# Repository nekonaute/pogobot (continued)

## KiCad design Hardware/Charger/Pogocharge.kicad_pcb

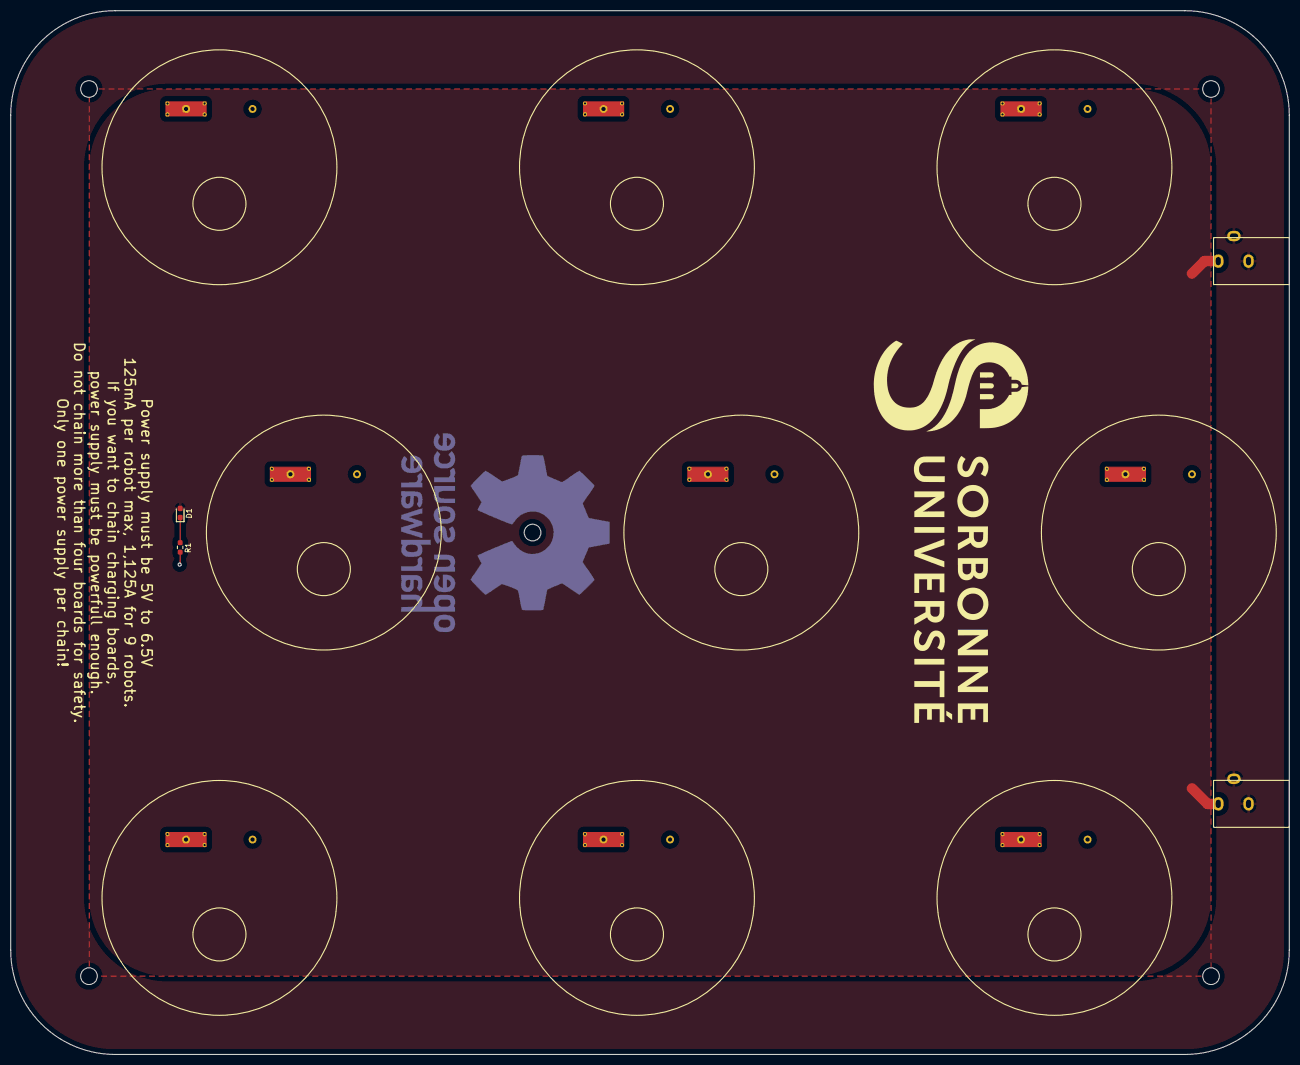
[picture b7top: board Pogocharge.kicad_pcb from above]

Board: 2 copper layers, 245.0 x 200.0 mm, 22 parts (0 on the bottom side), 3 nets.

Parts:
D1: LED; LED_0603_1608Metric_Pad1.05x0.95mm_HandSolder
J1, J4: Barrel_Jack_Switch; Barrel Jack_SparkFun_PRT-10811
J6, J8, J9, J10, J11, J19, J20, J21, J22: 90224-AS; 90224-AS-plus
J12, J13, J15, J16, J17, J23, J24, J25, J26: 90224-AS; 90224-AS-minus
R1: 10k; R_0603_1608Metric_Pad0.98x0.95mm_HandSolder

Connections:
+5V: D1.2 (A), J1.1, J4.1
GND: J1.2, J1.3, J4.2, J4.3, J12.1, J13.1, J15.1, J16.1, J17.1, J23.1, J24.1, J25.1, J26.1, R1.2
unnamed: D1.1 (K), R1.1

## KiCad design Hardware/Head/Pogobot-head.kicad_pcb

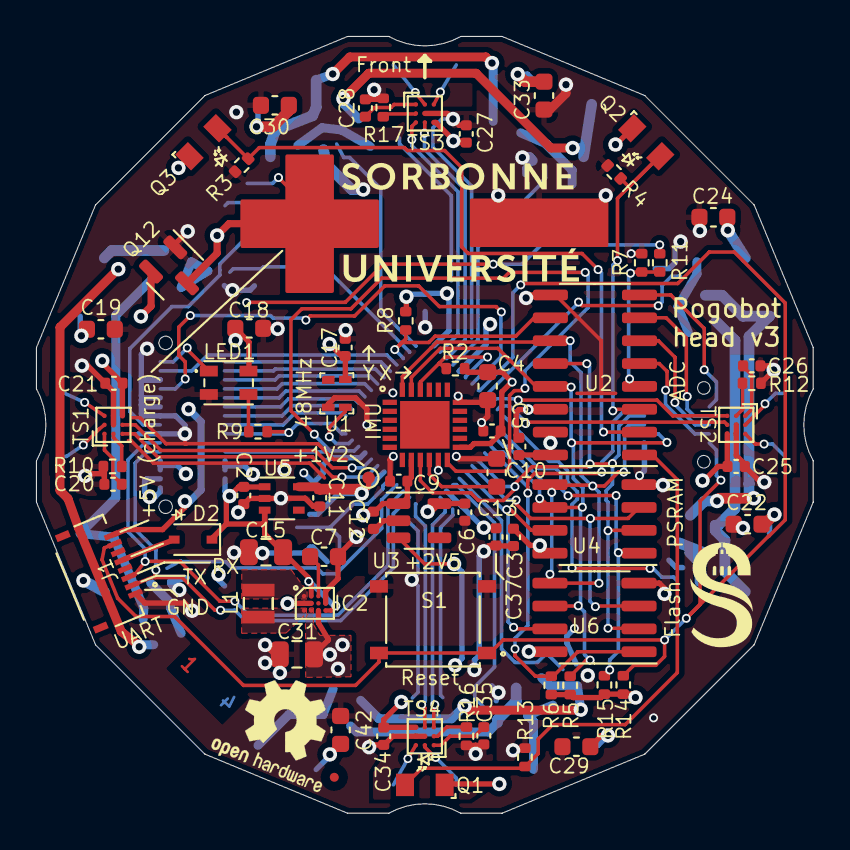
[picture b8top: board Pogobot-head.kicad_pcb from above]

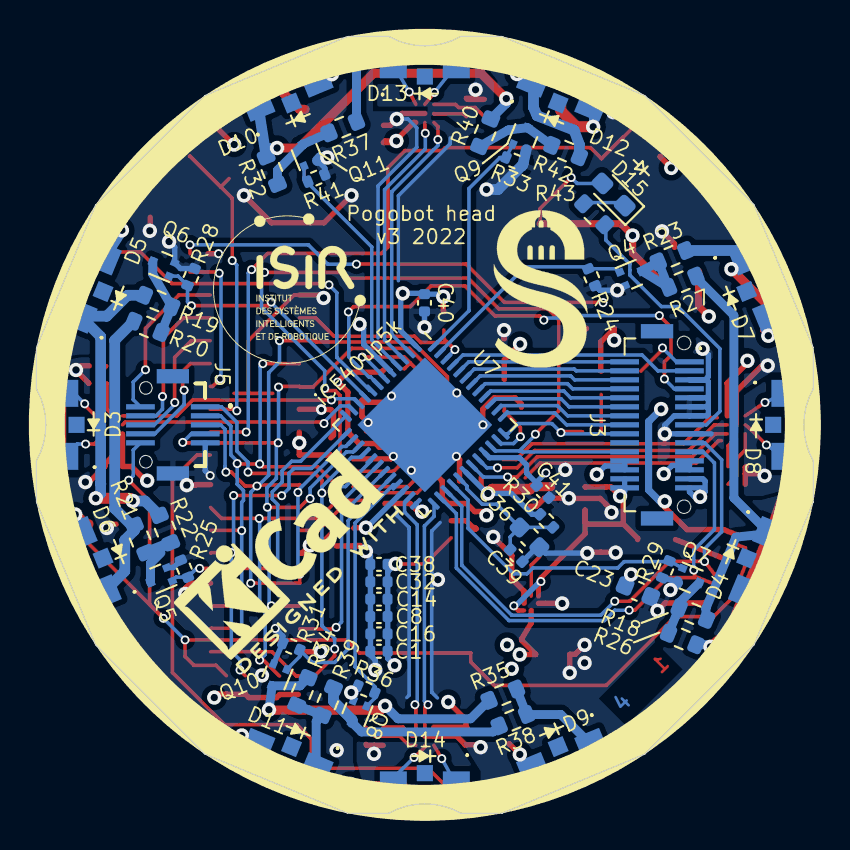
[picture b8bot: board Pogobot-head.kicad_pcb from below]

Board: 4 copper layers, 43.2 x 43.2 mm, 136 parts (64 on the bottom side), 98 nets.

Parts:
C1, C2, C5, C6, C11, C12, C14, C20, C26, C28, C35: 1uF; C_0402_1005Metric
C3, C16, C17, C37, C38, C39, C40, C41: 100nF; C_0402_1005Metric
C4: 2.2uF, X5R; C_0603_1608Metric
C7: 1uF, 10V; C_0603_1608Metric
C8, C32: 10nF; C_0402_1005Metric
C9: 10nF, X7R; C_0402_1005Metric
C10, C21, C25, C27, C34: 100nF, X7R; C_0402_1005Metric
C13: 470nF, X7R; C_0603_1608Metric
C15: 10uF, 10V; C_0805_2012Metric
C18, C36: 10uF; C_0603_1608Metric
C19, C22, C23, C24, C29, C30, C33, C42: 10uF, 6V; C_0603_1608Metric
C31: 22uF, 6V; C_0805_2012Metric
D2: 1N4448WS; D_SOD-323
D3, D8, D13, D14: VEMD10940F; VEMD10940FX01
D4, D5, D6, D7, D9, D10, D11, D12: VSMB10940
D15: LED; LED_0603_1608Metric_Pad1.05x0.95mm_HandSolder
IC1: ICM-20689; QFN50P400X400X95-25N-D
IC2: MAX77827DEWC+T; BGA12C40P4X3_201X161X69
J1: 2328702-8; 23287028
J3: 10132798-032100LF; 10132798032100LF
J5: 10132798-012100LF; 10132798012100LF
L1: MEKK2016H1R0M 1.0uH 41mOhms 4.5A; MEKK2016H
LED1: IN-PI22TAT5R5G5B; INPI22TAT5R5G5B
LOGO01: OSHW-Logo2_7.3x6mm_SilkScreen
LOGO02: KiCad-Logo2_5mm_SilkScreen
LOGO03: LOGO; LOGO_SU_without_text
LOGO04: LOGO; logo_isir_moyen
Q1, Q2, Q3: SFH 3710-Z; SFH3710
Q4, Q5, Q6, Q7, Q8, Q9, Q10, Q11: NTK3134NT5G; SOT-723
Q12: Q_PMOS_GSD; SOT-23
R2, R5, R6, R7, R8, R11, R14, R15, R24, R25, R28, R29, R31, R33, R36, R41: 10K; R_0402_1005Metric
R3, R4, R13: 1M; R_0402_1005Metric
R9: 330; R_0402_1005Metric
R10, R12, R16, R17: 15K; R_0402_1005Metric
R18, R19, R20, R26, R32, R37, R38, R39: 3; R_0603_1608Metric
R21, R22, R23, R27, R34, R35, R40, R42: 6; R_0603_1608Metric
R30: 100; R_0402_1005Metric
R43: 1K; R_0603_1608Metric
S1: PTS526_SM15_SMTR2_LFS; PTS526SK15SMTR2LFS
TP1: Testpoint; TestPoint_Pad_D0.7mm
TP2: TestPoint; Plus
TP3: TestPoint; Minus
TS1, TS2, TS3, TS4: TS4231; BGA-9_1.6x1.6mm_Layout3x3_P0.5mm
U1: DSC6101MI2B-048.0000; 4-Lead 2.0 mm x 1.6 mm VFLGA
U2: MCP3008; SOIC-16_3.9x9.9mm_P1.27mm
U3: MIC5504-2.5YM5; SOT-23-5
U4: LY68L6400; SOIC-8_3.9x4.9mm_P1.27mm
U5: MIC5365-1.2YC5; SOT-353_SC-70-5
U6: W25Q16JVSNIM; SOIC-8_3.9x4.9mm_P1.27mm
U7: ICE40UP5K-SG48; QFN-48-1EP_7x7mm_P0.5mm_EP5.3x5.3mm

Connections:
+1V2: C1.1, C8.1, C11.1, C14.1, C16.1, C32.1, C38.1, R30.2, TP1.1, U3.3 (EN), U5.5 (VOUT), U7.5 (VCC), U7.30 (VCC)
+2V5: C6.1, U3.5 (VOUT), U7.24 (VPP_2V5)
+3V3: C3.1, C4.1, C5.1, C9.1, C10.1, C12.1, C17.1, C18.1, C19.1, C21.1, C22.1, C23.1, C24.1, C25.1, C27.1, C29.1, C30.1, C31.1, C33.1, C34.1, C37.1, C40.1, C41.1, C42.1, D4.2, D5.2, D6.2, D7.2, D9.2, D10.2, D11.2, D12.2, IC1.8 (VDDIO), IC1.13 (VDD), IC2.C2 (OUT), IC2.C3 (OUTS), J3.12, J3.13, J3.18, J3.19, LED1.4 (VDD), Q1.1 (C), Q2.1 (C), Q3.1 (C), R2.1, R5.1, R6.1, R8.1, R14.1, R15.1, TS1.C3 (DVDD), TS2.C3 (DVDD), TS3.C3 (DVDD), TS4.C3 (DVDD), U1.4 (VDD), U2.15 (Vref), U2.16 (Vdd), U3.1 (VIN), U4.8 (VCC), U6.8 (VCC), U7.1 (VCCIO_2), U7.22 (SPI_VCCIO1), U7.33 (VCCIO_0)
+5V: J3.14, J3.15, Q12.2 (S)
+BATT: C2.1, C15.1, D2.1 (K), IC2.A2 (IN), IC2.C4 (EN), J3.16, J3.17, R11.1, U5.1 (VIN), U5.3 (EN)
/Back: Q1.2 (E), R13.1, U2.1 (CH0)
/CH4: J5.7, U2.5 (CH4)
/CH5: J5.8, U2.6 (CH5)
/CH6: J5.9, U2.7 (CH6)
/CH7: J5.10, U2.8 (CH7)
/Charge: D15.2 (A), J1.8, Q12.3 (D), TP2.1
/LX1: IC2.A1 (LX1), L1.2
/LX2: IC2.C1 (LX2), L1.1
/Left: Q3.2 (E), R3.1, U2.2 (CH1)
/OSC_IN: U1.3 (OUT), U7.35 (IOT_46B_G0)
/Right: Q2.2 (E), R4.1, U2.3 (CH2)
/VBat_control: R7.1, R11.2, U2.4 (CH3)
/VCCPLL: C36.1, C39.1, R30.1, U7.29 (VCCPLL)
/sheetReceive_Back/AVDD: C35.1, TS4.A1 (AVDD)
/sheetReceive_Back/IIN+: D14.2 (A), TS4.A2 (IIN+)
/sheetReceive_Back/IIN-: D14.1 (K), TS4.A3 (IIN-)
/sheetReceive_Back/RBIAS: R16.2, TS4.B1 (RBIAS)
/sheetReceive_Front/AVDD: C28.1, TS3.A1 (AVDD)
/sheetReceive_Front/IIN+: D13.2 (A), TS3.A2 (IIN+)
/sheetReceive_Front/IIN-: D13.1 (K), TS3.A3 (IIN-)
/sheetReceive_Front/RBIAS: R17.2, TS3.B1 (RBIAS)
/sheetReceive_Left/AVDD: C20.1, TS1.A1 (AVDD)
/sheetReceive_Left/IIN+: D8.2 (A), TS1.A2 (IIN+)
/sheetReceive_Left/IIN-: D8.1 (K), TS1.A3 (IIN-)
/sheetReceive_Left/RBIAS: R10.2, TS1.B1 (RBIAS)
/sheetReceive_Right/AVDD: C26.1, TS2.A1 (AVDD)
/sheetReceive_Right/IIN+: D3.2 (A), TS2.A2 (IIN+)
/sheetReceive_Right/IIN-: D3.1 (K), TS2.A3 (IIN-)
/sheetReceive_Right/RBIAS: R12.2, TS2.B1 (RBIAS)
ADC_CSn: R8.2, U2.10 (~CS/SHDN), U7.46 (IOB_0A)
CDONE: J3.4, U7.7 (CDONE)
Emit1_B: Q10.1 (G), R31.1, U7.20 (IOB_25B_G3)
Emit1_F: Q9.1 (G), R33.1, U7.48 (IOB_4A)
Emit1_L: Q4.1 (G), R24.1, U7.47 (IOB_2A)
Emit1_R: Q5.1 (G), R25.1, U7.12 (IOB_22A)
Emit2_B: Q8.1 (G), R36.1, U7.21 (IOB_23B)
Emit2_F: Q11.1 (G), R41.1, U7.4 (IOB_8A)
Emit2_L: Q7.1 (G), R29.1, U7.28 (IOT_41A)
Emit2_R: Q6.1 (G), R28.1, U7.9 (IOB_16A)
FLASH_CS: J5.1, R6.2, U6.1 (~CS), U7.16 (IOB_35b_SPI_CSN)
GND: C1.2, C2.2, C3.2, C4.2, C5.2, C6.2, C7.2, C8.2, C9.2, C10.2, C11.2, C12.2, C13.2, C14.2, C15.2, C16.2, C17.2, C18.2, C19.2, C20.2, C21.2, C22.2, C23.2, C24.2, C25.2, C26.2, C27.2, C28.2, C29.2, C30.2, C31.2, C32.2, C33.2, C34.2, C35.2, C36.2, C37.2, C38.2, C39.2, C40.2, C41.2, C42.2, IC1.11 (FSYNC), IC1.18 (GND), IC2.A4 (AGND), IC2.B1 (PGND), IC2.B2 (FPWM), IC2.B4 (SEL), J1.1, J3.3, J3.5, J3.6, J3.7, J3.9, J5.5, J5.MP2, LED1.2 (VSS), Q4.2 (S), Q5.2 (S), Q6.2 (S), Q7.2 (S), Q8.2 (S), Q9.2 (S), Q10.2 (S), Q11.2 (S), Q12.1 (G), R3.2, R4.2, R7.2, R10.1, R12.1, R13.2, R16.1, R17.1, R24.2, R25.2, R28.2, R29.2, R31.2, R33.2, R36.2, R41.2, S1.3 (NO_1), S1.4 (NO_2), TP3.1, TS1.B2 (AVSS), TS1.B3 (AVSS2), TS2.B2 (AVSS), TS2.B3 (AVSS2), TS3.B2 (AVSS), TS3.B3 (AVSS2), TS4.B2 (AVSS), TS4.B3 (AVSS2), U1.2 (GND), U2.9 (DGND), U2.14 (AGND), U3.2 (GND), U4.4 (VSS), U5.2 (GND), U6.4 (GND), U7.49 (PAD/GND)
GPIO0: J3.30, U7.44 (IOB_3B_G6)
GPIO1: J3.29, U7.43 (IOT_49A)
GPIO2: J3.28, U7.42 (IOT_51A)
GPIO3: J3.27, U7.41 (RGB2)
GPIO4: J3.26, U7.40 (RGB1)
GPIO5: J3.25, U7.39 (RGB0)
GPIO6: J3.24, U7.38 (IOT_50B)
GPIO7: J3.23, U7.37 (IOT_45A_G1)
GPIO8: J3.2, U7.45 (IOB_5B)
IMU_CSn: IC1.22 (NCS), R2.2, U7.6 (IOB_13B)
IMU_INT: IC1.12 (INT), J3.20, U7.34 (IOT_44B)
LED_CHARGE: J3.8, R43.2
unnamed: C7.1, IC2.A3 (BIAS)
unnamed: C13.1, IC1.10 (REGOUT)
unnamed: D2.2 (A), J1.5
unnamed: D4.1, R18.1, R27.1
unnamed: D5.1, R20.1, R22.1
unnamed: D6.1, R19.1, R21.1
unnamed: D7.1, R23.1, R26.1
unnamed: D9.1, R35.1, R38.1
unnamed: D10.1, R32.1, R40.1
unnamed: D11.1, R34.1, R39.1
unnamed: D12.1, R37.1, R42.1
unnamed: D15.1 (K), R43.1
unnamed: LED1.3 (DIN), R9.1
unnamed: Q4.3 (D), R23.2, R27.2
unnamed: Q5.3 (D), R21.2, R22.2
unnamed: Q6.3 (D), R19.2, R20.2
unnamed: Q7.3 (D), R18.2, R26.2
unnamed: Q8.3 (D), R38.2, R39.2
unnamed: Q9.3 (D), R40.2, R42.2
unnamed: Q10.3 (D), R34.2, R35.2
unnamed: Q11.3 (D), R32.2, R37.2
RAM_CS: R15.2, U4.1 (~CE), U7.13 (IOB_24A)
RGB_LED_IN: J3.22, R9.2, U7.36 (IOT_48B)
RGB_LED_OUT: J3.1, LED1.1 (DOUT)
SPI_CLK: IC1.23 (SCL/SCLK), J5.4, R5.2, U2.13 (CLK), U4.6 (SCLK), U6.6 (CLK), U7.15 (IOB_34a_SPI_SCK)
SPI_MISO: IC1.9 (AD0/SDO), J5.2, U2.12 (Dout), U4.2 (SO/SIO), U6.2 (DO/IO1), U7.17 (IOB_33b_SPI_SI)
SPI_MOSI: IC1.24 (SDA/SDI), J5.3, U2.11 (Din), U4.5 (SI/SIO), U6.5 (DI/IO0), U7.14 (IOB_32a_SPI_SO)
SPI_~HLD-IO3: U4.7 (SIO3), U6.7 (~HLD/~RST/IO3), U7.19 (IOB_29B)
SPI_~WP-IO2: U4.3 (SIO2), U6.3 (~WP/IO2), U7.18 (IOB_31B)
TSDATA_B: TS4.C1 (D), U7.23 (IOT_37A)
TSDATA_F: TS3.C1 (D), U7.2 (IOB_6A)
TSDATA_L: TS1.C1 (D), U7.31 (IOT_42B)
TSDATA_R: TS2.C1 (D), U7.10 (IOB_18A)
TSENV_B: TS4.C2 (E), U7.25 (IOT_36B)
TSENV_F: TS3.C2 (E), U7.3 (IOB_9B)
TSENV_L: TS1.C2 (E), U7.32 (IOT_43A)
TSENV_R: TS2.C2 (E), U7.11 (IOB_20A)
iCE_RX: J1.3, J3.10, U7.27 (IOT_38B)
iCE_TX: J1.2, J3.11, U7.26 (IOT_39A)
~RESET: J1.7, J5.6, R14.2, S1.1 (COM_1), S1.2 (COM_2), U7.8 (CRESET_B)

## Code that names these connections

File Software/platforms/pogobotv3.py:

# POGOBOT
# Copyright © 2022 Sorbonne Université ISIR
# This file is licensed under the Expat License, sometimes known as the MIT License. 
# Please refer to file LICENCE for details.

# Pogobot design based on Fomu:
# - Crowd Supply campaign: https://www.crowdsupply.com/sutajio-kosagi/fomu
# - Design files: https://github.com/im-tomu/fomu-hardware/tree/evt/hardware/pcb

from litex.build.generic_platform import *
from litex.build.lattice import LatticePlatform
from litex.build.lattice.programmer import IceStormProgrammer

# IOs ----------------------------------------------------------------------------------------------

_io = [
    ("clk48", 0, Pins("35"), IOStandard("LVCMOS33")),

    ("user_led", 0, Pins("36"), IOStandard("LVCMOS33")),

    ("serial", 0,
        Subsignal("tx", Pins("26")),
        Subsignal("rx", Pins("27")),
        IOStandard("LVCMOS33")
    ),

    ("spiflash", 0,
        Subsignal("cs_n", Pins("16"), IOStandard("LVCMOS33")),
        Subsignal("clk",  Pins("15"), IOStandard("LVCMOS33")),
        Subsignal("miso", Pins("17"), IOStandard("LVCMOS33")),
        Subsignal("mosi", Pins("14"), IOStandard("LVCMOS33")),
        Subsignal("wp",   Pins("18"), IOStandard("LVCMOS33")),
        Subsignal("hold", Pins("19"), IOStandard("LVCMOS33")),
    ),

    ("spiflash4x", 0,
        Subsignal("cs_n", Pins("16"), IOStandard("LVCMOS33")),
        Subsignal("clk",  Pins("15"), IOStandard("LVCMOS33")),
        Subsignal("dq",   Pins("14 17 18 19"), IOStandard("LVCMOS33")),
    ),
    ("ir_tx", 0, #Front, 1=L, 2=H
        Subsignal("H", Pins("4")),
        Subsignal("L", Pins("48")),
        IOStandard("LVCMOS33")
    ),
    ("ir_tx", 1, #Right
        Subsignal("H", Pins("9")),
        Subsignal("L", Pins("12")),
        IOStandard("LVCMOS33")
    ),
    ("ir_tx", 2, #Back
        Subsignal("H", Pins("21")),
        Subsignal("L", Pins("20")),
        IOStandard("LVCMOS33")
    ),
    ("ir_tx", 3, #Left
        Subsignal("H", Pins("28")),
        Subsignal("L", Pins("47")),
        IOStandard("LVCMOS33")
    ),
    ("TS4231", 0, #Front
         Subsignal("D", Pins("2")),
         Subsignal("E", Pins("3")),
         IOStandard("LVCMOS33")
    ),
    ("TS4231", 1, #Right
         Subsignal("D", Pins("10")),
         Subsignal("E", Pins("11")),
         IOStandard("LVCMOS33")
    ),
    ("TS4231", 2, #Back
         Subsignal("D", Pins("23")),
         Subsignal("E", Pins("25")),
         IOStandard("LVCMOS33")
    ),
    ("TS4231", 3, #Left
         Subsignal("D", Pins("31")),
         Subsignal("E", Pins("32")),
         IOStandard("LVCMOS33")
    ),

    ("adc_cs_n", 0, Pins("46"), IOStandard("LVCMOS33")),
    ("imu_cs_n", 0, Pins("6"), IOStandard("LVCMOS33")),
    ("ram_cs_n", 0, Pins("13"), IOStandard("LVCMOS33")),

    ("imu_int", 0, Pins("34"), IOStandard("LVCMOS33")),
]

# Connectors ---------------------------------------------------------------------------------------

_connectors = [
    # Left connector, J3, 30 pins (from top view)
    # Right connector, J5, 10 pins

    # Complete pinout :
    # 1 : RGB_LED_OUT (connected to output of head's RGB LED)
    # 2 : GPIO8
    # 3 : GND
    # 4 : CDONE
    # 3,5-7,,9 : GND
    # 8 : LED_Charge
    # 10 : iCE_RX
    # 11 : iCE_TX
    # 12,13,18,19 : +3.3V
    # 14,15 : +5V (charge)
    # 16,17 : +Batt
    # 20 : IMU_INT
    # 21 : unused
    # 22 : RGB_LED_IN (connected to iCE40)
    # 23 : GPIO7
    # 24 : GPIO6
    # 25 : GPIO5
    # 26 : GPIO4
    # 27 : GPIO3
    # 28 : GPIO2
    # 29 : GPIO1
    # 30 : GPIO0

    # usable pins connected to FPGA :
    # pin :   30 29 28 27 26 25 24 23  2 4 22
    ("GPIO", "44 43 42 41 40 39 38 37 45 7 36")
    # index :  0  1  2  3  4  5  6  7  8 9 10

    # J5 pinout, nothing really configurable here
    # 1 : FLASH_CS
    # 2 : SPI_MISO
    # 3 : SPI_MOSI
    # 4 : SPI_CLK
    # 5 : GND
    # 6 : RESET_n
    # 7 : ADC channel 4
    # 8 : ADC channel 5
    # 9 : ADC channel 6
    # 10 : ADC channel 7

]

# Platform -----------------------------------------------------------------------------------------

class Platform(LatticePlatform):
    default_clk_name   = "clk48"
    default_clk_period = 1e9/48e6

    def __init__(self):
        LatticePlatform.__init__(self, "ice40-up5k-sg48", _io, _connectors, toolchain="icestorm")

    def create_programmer(self):
        return IceStormProgrammer()

    def do_finalize(self, fragment):
        LatticePlatform.do_finalize(self, fragment)
        self.add_period_constraint(self.lookup_request("clk48", loose=True), 1e9/48e6)

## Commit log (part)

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2022-07-05 initial commit for Hardware / Tools and Readme
2022-07-05 adding footprints and symbols
2022-07-05 Added index.html
2022-07-05 Set theme jekyll-theme-cayman
2022-07-05 adding usb uart program board
2022-07-08 update license
2022-07-08 adding pogodocs.md
2022-07-08 updating README with some todo
2022-07-08 initial Software commit
2022-07-08 bugfix typo
2022-07-08 correction global Makefile
2022-07-08 removing warning
2022-07-08 adding links to pogodocs.md
2022-07-08 adding doc generation info
2022-07-12 fixes bugs on sdk generation
2022-07-12 corrects typos and mistakes
2022-08-17 adding memory map
2022-09-17 Last modifications to make v3 work, and some cleanup
2022-09-22 improve SPI flashing documentation
2022-09-26 adding PCB v3 addons
2022-09-26 adding pogobot charger
2022-09-27 adding baterry life visualisation
2022-09-30 adding start, stop, user msg, bat from the remote
2022-09-30 adding ts4231 sleep and wakeup
2022-10-04 adding goto sleep for the IMU
2022-10-04 adding standby mode command
2022-10-04 constant IR number correction
2022-10-04 bugfix range color led voltage
2022-10-04 changing boot banner
2022-10-04 changing standby led intensity
2022-10-05 adding voltage mode
2022-10-05 adding voltage mode command
2022-10-05 adding msg type enum
2022-10-05 Changing all IR messages over slip message
2022-10-10 adding little cercle on the charger
2022-10-10 changing the led behavior of standby
2022-10-10 adding the flash message type
2022-10-11 first ir flashing version (no error mgt)
2022-10-12 correction of the SPI base flash
2022-10-12 updating user prog erase
2022-10-12 updating the command rc_erase
2022-10-12 update flash astatus and adding flash partial
2022-10-12 Fixed path removed in kicad files, symlinks added
2022-10-13 minor changes in boot.c
2022-10-13 adding first version for partial programming
2022-10-13 adding autotest mode
2022-10-13 all fixed links replaced by
2022-10-13 removed cache and .gitignore added
2022-10-17 blocking programming if already programmed
2022-10-17 adding IR Remote info
2022-10-18 adding remote screw info
2022-10-18 addinf remote 3D files
2022-10-18 adding protection on erase user prog
2022-10-20 correction on READMEs
2022-10-24 bug correction flashing
2022-11-09 pip3 in sudo mode
2023-01-05 update 3d models
2023-01-05 update 3d printing info on readme
2023-01-16 add singularity def file + how to use it in README
2023-01-16 fix singularity install in README
2023-01-17 updating Readme (cross compiler / dialout groups)
2023-01-20 updating/correcting sdk generator
2023-01-23 renamed singularity file to 'pogobot.def'
2023-03-17 reduce timing during upload
2023-03-24 adding photosensor continue probing
2023-03-29 fixing bug for charger
2023-04-11 adds bidirectionnal motor command
2023-04-12 bug fix on spi_sr_register and test functions
2023-04-20 change to pogobot v3 as default
2023-04-20 bugfix non compiling examples
2023-06-13 adding autocalibration example
2023-06-13 modify IR timing to slow down transmission and improve stability
2023-06-13 adding remote and remote strip
2023-06-16 adding blocking run if flash not ok
2023-06-30 correcting sensor order
2023-06-30 correcting sdk generation
2023-06-30 adding info, change functions name, adding bios cmd
2023-06-30 removing logo to gain space in memory
2023-06-30 adding memorisation of motor dir
2023-06-30 remove ann_test to free some space
2023-06-30 warning correction
2023-06-30 adding auto upload motor direction inside pogobot init
2023-06-30 adding bios command to memorize motor direction
2023-06-30 /!\ removing 16bits from the header, no more compatible
2023-06-30 replace the logo
2023-06-30 adding power motor management in comment
2023-07-03 bug fix get/set power motor + cleanup to gain space
2023-07-04 adding set motor power mem
2023-08-28 correcting all send bios and usr message
2023-08-29 improve gitignore
2023-08-29 adding new hardware elements (pogo_object, active wall)
2023-08-29 remove warnings over KiKad6
2023-08-29 bugfix: typo in function definition
2023-08-29 update pogodocs
2023-08-30 adding pogobject software directories
2023-09-01 adding battery voltage monitoring
2023-09-01 adding pogodocs inside the sdk
2023-09-04 adding battery control inside the webapp
2023-09-04 adding battery control, change object name and had a missing declaration
2023-09-06 upgrade wall led strip from 20cm to 50cm
2023-09-12 adding binaries to rapidily install robots
2023-09-12 changing the size of the strip led from 50 to 30cm
2023-09-20 update automatic cmd inside pogobject interface
2023-09-20 modify color palet for pogobject interface
2023-09-25 improve bat visu and update, change all green
2023-09-26 correcting warning
2023-09-26 adding comment debug to slip protocole
2023-09-26 adding short header message capability + example
2023-09-26 adding float test example
2023-09-29 correcting missleading printf
2023-09-29 updating docs
2023-10-02 adding binary of version 2.2
2023-10-05 improved readme for pogobject
2023-10-05 adding first version of pogoWallApp
2023-10-05 adding the binary installer for x64 debian distribution
2023-10-13 improving pogobject visual communication
2023-10-13 update pogobject readme
2023-10-20 repairing not working ir programmation
2023-10-23 adding release.h and the print helper, update doc
2023-10-23 adding release version inside the pogobios
2023-10-23 creating a tool to prepare a new version folder
2023-10-23 adding binaries of the v2.2.1 - fixes the programming by IR problem
2023-10-23 removing the auto reboot after programing a robot with serialboot
2023-10-23 improved Readme.md
2023-11-07 correcting a too much buffer allocation
2023-11-13 adding images.json example
2023-11-14 adding readme for binaries
2023-11-15 correcting readme
2023-11-16 updating readme from binaries
2023-11-16 changes the cmd to program the robot from IR (rc_flash_robot)
2023-11-17 improves binaries readme
2023-11-17 blocks the meson version
2023-12-20 adding MAC adress display if needed
2023-12-21 Adding time API to the documentation
    add the missing pogobot_timer_sleep_stopwatch.c API to the `.md`
2023-12-21 updating the pogobjectWebControl
2024-01-09 correcting cmd name in helper
2024-01-09 improves installation script
2024-01-15 add the wifi configuration of pogobject by wifi
2024-01-15 updates the pogobject readme
2024-01-15 updates the pogobject pcb to include config mode
2024-01-15 divides the readme in parts
2024-01-16 continues to re organize the readme
2024-01-18 fix bug on missing write to eeprom
2024-01-26 changes the API and corrects names (API 2.3)
2024-02-01 updates hardware readme
2024-02-01 updates software readme
2024-02-08 changing timing of recurent cmds
2024-02-09 IR message API massive update + remove receiver_id in header
2024-02-09 adding missing bin and v2.4 bin (IR API changes)
2024-02-12 update resistance values
2024-02-13 docs text correction
2024-03-07 adding missing identification
2024-03-07 merging pogobot.h and stopwatch.h
2024-03-07 changing API version tag
2024-03-13 adjust timing to allow correct programmation
2024-03-14 update v2.4 bin
2024-06-18 fix the changing sending crc
2024-06-25 modification crcitt to 32 bits
2024-07-04 adding bin v2.5 (crc32)
2024-10-17 add memcpy protection
2024-10-23 add test around the CRC
2024-10-23 add double payload size verification
2024-10-23 missing 2.5 update
2024-11-04 add the ir flash with double verif
2024-11-04 add new version
2024-11-04 add v2.6 binaries
2025-01-13 adds 12v leds schematic
2025-01-13 change transistor in wall crtl
2025-06-04 Add pogowall ctrl 3d models
2025-09-10 adding belly v3
2025-09-11 missing files for v3
2025-11-26 fix: typos in information prints
2026-03-11 SDK 2.7 : user can write in flash, user can mute robot IR, user can reset IR RX flags
2026-03-12 Correcting test_read_write_flash main
2026-03-12 fixing minor pb
2026-03-12 adding sdk 2.7 changes
2026-03-13 Add install_APIv2.7
2026-04-24 Add magnetometer librariry to make measurements on the LIS2MDL
2026-05-12 Moved 3d-addons
2026-05-12 Create folder docs/
2026-05-12 Fixed broken link in README.md
2026-05-12 Update 3d-addons to 2026 models
2026-05-12 Restructure main README.md
2026-05-12 Add Pogobot2026 stl files
2026-05-12 Remove old api documentation
2026-05-12 Replace old api doc with Doxygen
2026-05-12 Move charger doc back to Hardware
2026-05-13 Add 3d-addons to README.md
2026-05-13 Fix wall doc references
2026-05-13 Unify spelling for Readme files name
2026-05-13 Add Software Guide for Users
2026-05-19 Remove ISIR specific doc
2026-06-29 Add comments to magnetometer code
2026-06-29 Update magnetometer doc
2026-06-30 v2.7 - Add binaries
2026-06-30 SDK 2.7 - Correcting documentation
